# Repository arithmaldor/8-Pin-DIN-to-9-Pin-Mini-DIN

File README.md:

# 8 Pin Din (270 deg) to 9 Pin Mini Din
It's what it says on the tin. For HDRetrovision Cables.

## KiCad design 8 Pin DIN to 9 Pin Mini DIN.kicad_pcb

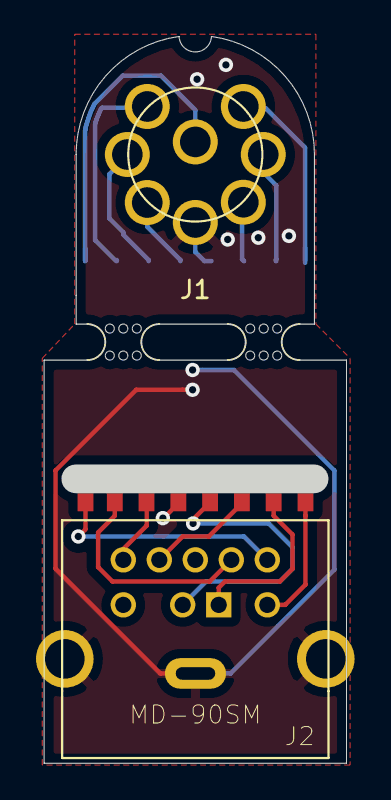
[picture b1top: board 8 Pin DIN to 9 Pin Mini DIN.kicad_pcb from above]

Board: 2 copper layers, 16.8 x 40.4 mm, 4 parts (0 on the bottom side), 8 nets.

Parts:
J1: DIN-8; 8_PIN_DIN_MALE
J2: MD-90SM; CUI_MD-90SM
mouse-bite-2mm-slot, mouse-bite-2mm-slot#2: VAL**; mouse-bite-2mm-slot

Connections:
5V: J1.4, J2.2
BLUE: J1.6, J2.1
GND: J1.2, J2.S, J2.S1
GREEN: J1.8, J2.3
LEFT: J1.1, J2.8
RED: J1.7, J2.7
RIGHT: J1.5, J2.9
SYNC: J1.3, J2.4

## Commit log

2019-07-03 increased spacing on 8 pin a bit, changed md-90sm to md-90s
2019-07-11 new and improved
2019-07-11 finished layout, generated gerbers
2019-07-29 adjusted footprints
